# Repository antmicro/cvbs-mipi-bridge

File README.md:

# Composite Video (CVBS) to MIPI CSI-2 bridge

Copyright (c) 2022-2025 [Antmicro](https://www.antmicro.com)

## Overview

This repository contains open hardware design files for a video bridge converting the analog composite video (CBVS) standard into MIPI CSI-2.
The video conversion is handled with Analog Devices [ADV7828-M](https://www.analog.com/media/en/technical-documentation/data-sheets/ADV7282.pdf) 10-bit 4x Oversampled SDTV Video Decoder.
The design files were prepared in KiCad.

## Repository structure

The main repository directory contains KiCad PCB project files, a LICENSE and README.
The remaining files are stored in the following directories:

* `lib` - contains the component libraries
* `img` - contains graphics for this README
* `doc` - contains pdf schematics
* `assets` - contains visual assets for showcasing this design on [Open Hardware Portal](https://openhardware.antmicro.com)

## Key Features

* Analog Devices ADV7282-M CVBS-to-MIPI video converter
* 4 analog video input channels exposed on RCA connectors
* A single 1-lane MIPI CSI-2 digital output interface

Please note that according to the datasheet the ADV7282-M includes an embedded analog multiplexer and processes only one analog input channel at a time.

This video accessory is electrically compatible with several video processing platforms created by Antmicro, such as:
 
* [Jetson Nano Baseboard](https://github.com/antmicro/jetson-nano-baseboard) supporting NVIDIA Jetson Nano, Jetson Xavier NX, Jetson TX2 NX
* [Google Coral Baseboard](https://github.com/antmicro/google-coral-baseboard)
* [Snapdragon 625 Baseboard](https://github.com/antmicro/snapdragon-625-baseboard)
* [Snapdragon 845 Baseboard](https://github.com/antmicro/snapdragon-845-baseboard)
* [AMD-Xilinx Kria K26 DevBoard](https://github.com/antmicro/kria-k26-devboard)

It can also be used with NVIDIA AGX Xavier and NVIDIA AGX Orin with a dedicated [adapter](https://github.com/antmicro/jetson-agx-csi-adapter).

## Board diagram

## License

[Apache-2.0](LICENSE)

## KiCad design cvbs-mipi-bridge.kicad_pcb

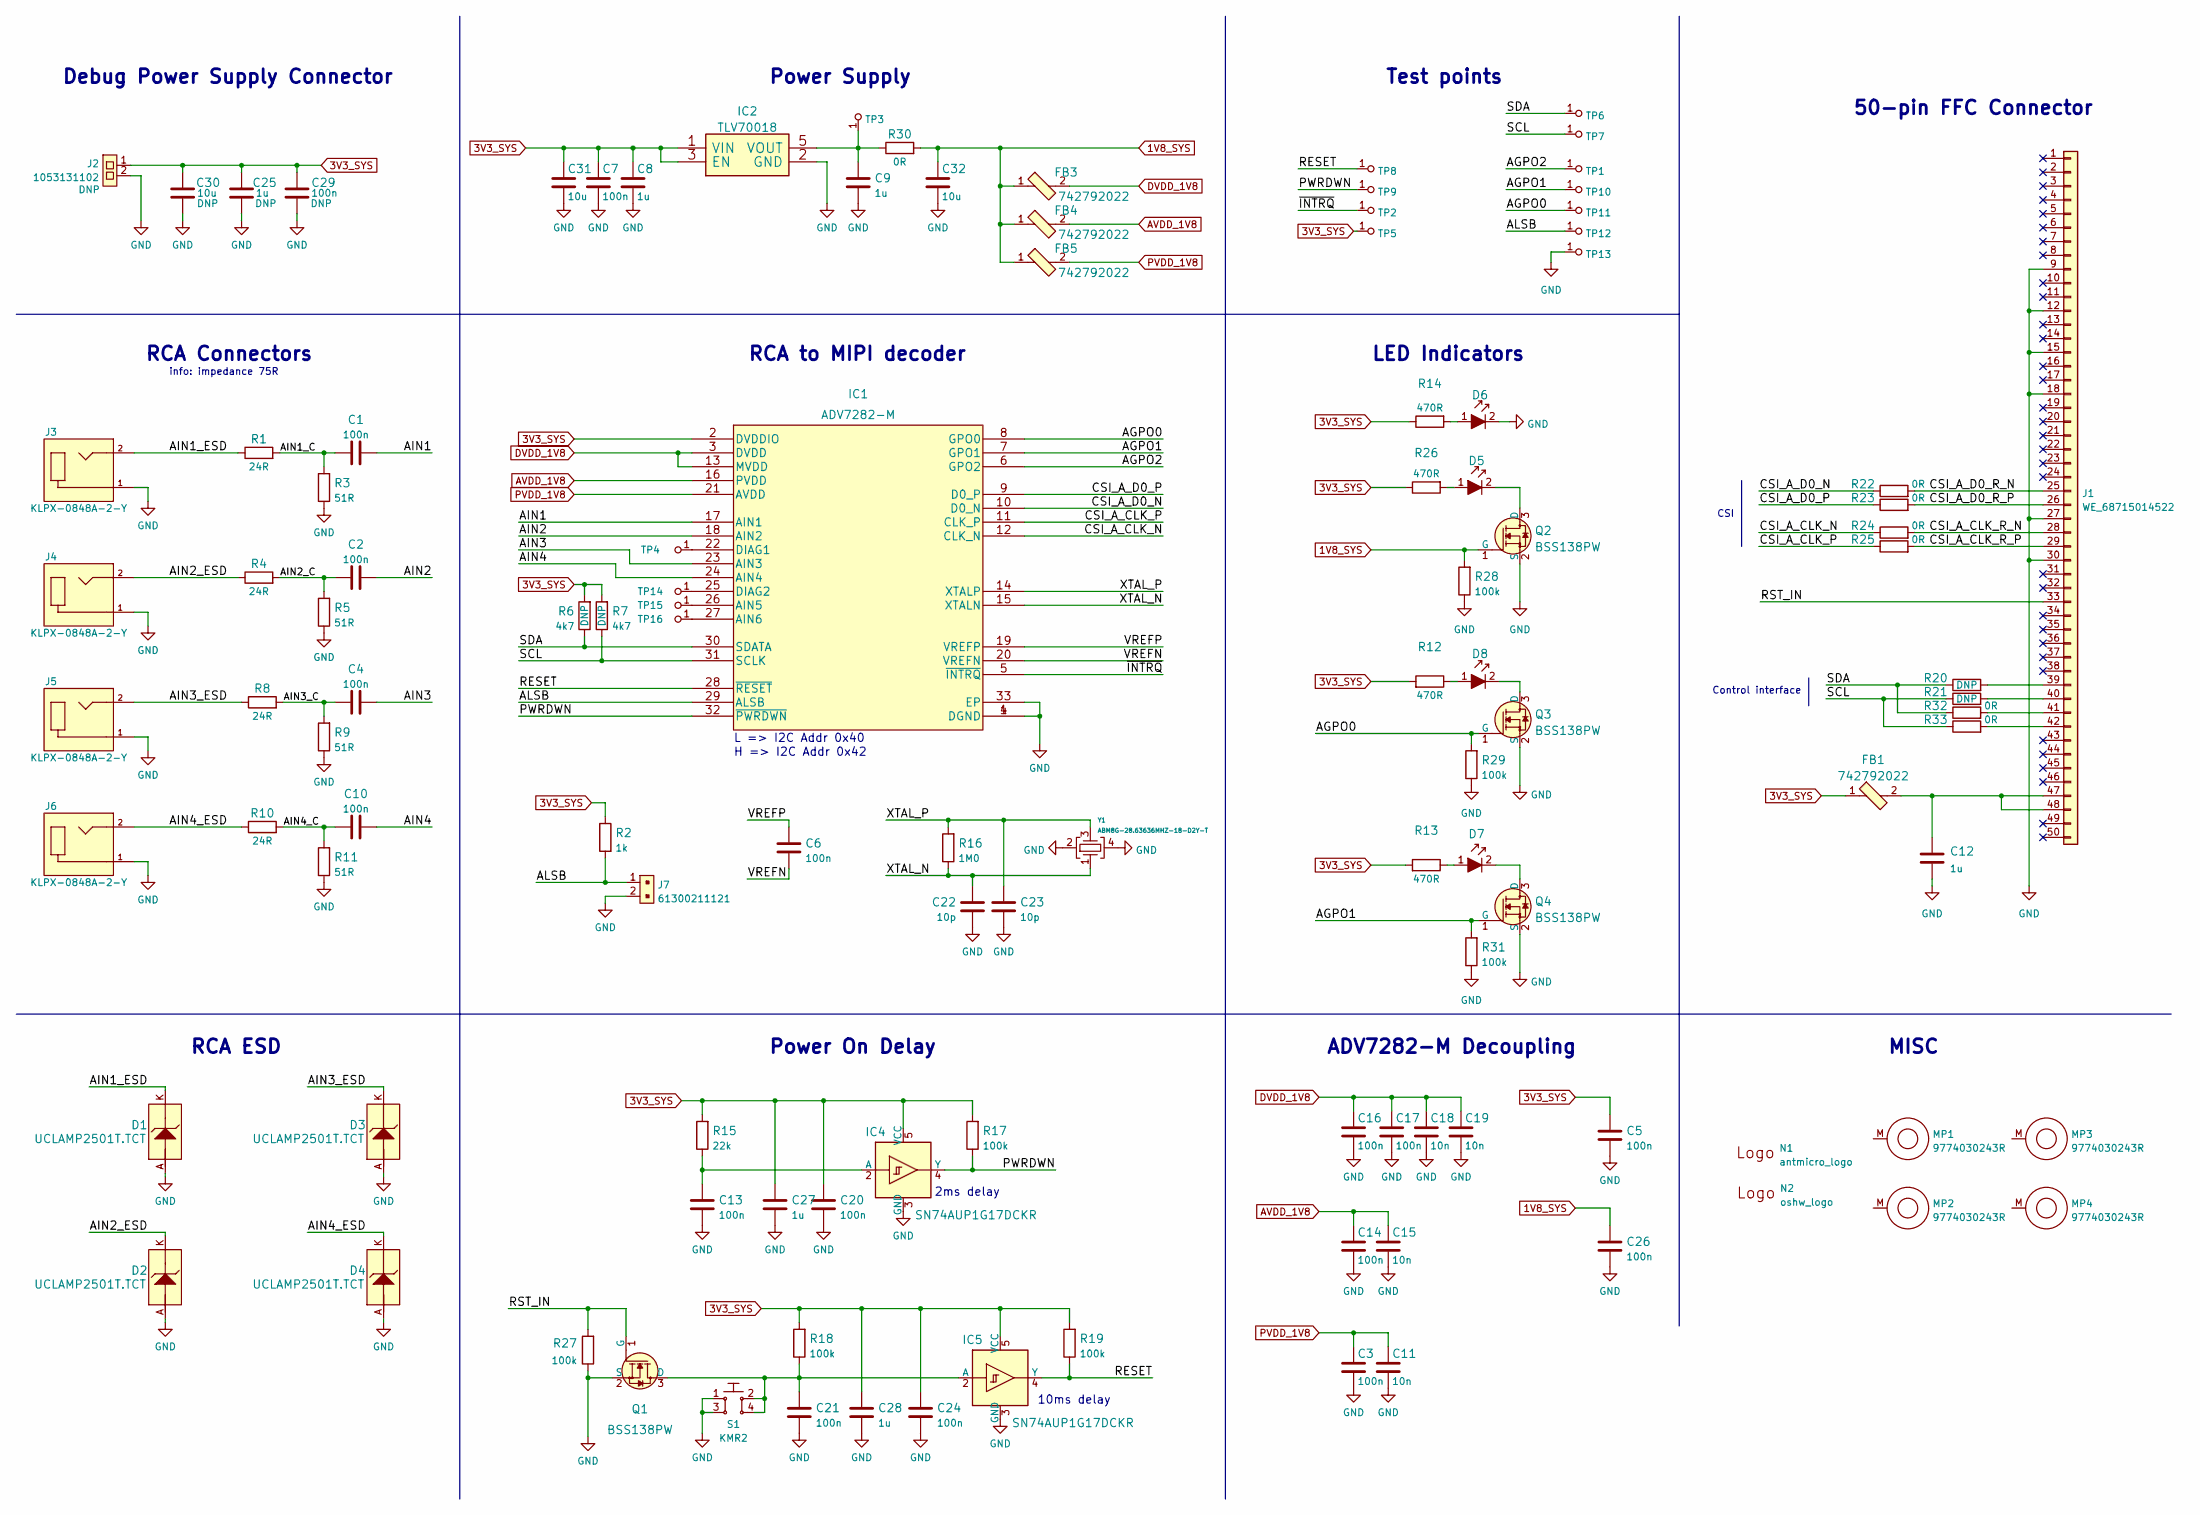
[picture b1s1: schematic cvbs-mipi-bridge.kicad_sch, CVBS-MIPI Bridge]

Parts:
C1, C2, C3, C4, C5, C6, C7, C10, C14, C16, C17, C26, C29: C_100n_0402; 0402-cap; MPN GRM155R61H104KE14D
C8, C9, C25: C_1u_0402; 0402-cap; MPN C1005X6S1A105K050BC
C11, C15, C18, C19: C_10n_0402; 0402-cap; MPN 04025G103ZAT2A
C12: C_1u_0603; 0603-cap; MPN 0603YD105KAT2A
C13, C20, C21, C24: C_100n_0402; 0402-cap_ThermalReliefs_ZoneSizeSettings; MPN GRM155R61H104KE14D
C22, C23: C_10p_0402; 0402-cap; MPN MC0402N100D500CT
C27, C28: C_1u_0402; 0402-cap_ThermalReliefs_ZoneSizeSettings; MPN C1005X6S1A105K050BC
C30, C31, C32: C_10u_0603; 0603-cap; MPN GRM188R61A106KE69D
D1, D2, D3, D4: UCLAMP2501T.TCT; SLP1006P2T; MPN UCLAMP2501T.TCT
D5, D7, D8: KP-1608ZGC; LED_0603; MPN KP-1608EC
D6: KP-1608ZGC; LED_0603_ThermalReliefs_ZoneSizeSettings; MPN KP-1608EC
FB1, FB3, FB4, FB5: 742792022; 0805-res; MPN 742792022
IC1: ADV7282-M; LFCSP-32-1EP-5x5mm; MPN ADV7282WBCPZ-M
IC2: TLV70018; SC-70-5; MPN TLV70018DCKR
IC4, IC5: SN74AUP1G17DCKR; SC-70-5; MPN SN74AUP1G17DCKR
J1: WE_68715014522; MPN 68715014522
J2: 1053131102; MPN 1053131102
J3, J4, J5, J6: KLPX-0848A-2-Y; MPN KLPX-0848A-2-Y
J7: 61300211121; PinHeader_1x2_P2.54_Drill0.9mm; MPN 61300211121
MP1, MP2, MP3, MP4: 9774030243R; MPN 9774030243R
N1: antmicro_logo; antmicro-logo_scaled_20mm_mask
N2: oshw_logo; oshw-logo
Q1, Q2, Q3, Q4: BSS138PW; SC70-3; MPN BSS138PW
R1, R4, R8, R10: R_24R_0402; 0402-res; MPN ERJ-2RKF24R0X
R2: R_1k_0402; 0402-res; MPN CR0402-FX-1001GLF
R3, R5, R9, R11: R_51R_0402; 0402-res; MPN RC0402FR-0751RL
R6, R7: R_4k7_0402; 0402-res; MPN MCS04020C4701FE000
R12, R13, R14, R26: R_470R_0402; 0402-res; MPN CRCW0402470RFKED
R15: R_22k_0402; 0402-res; MPN ERJ-2RKF2202X
R16: R_1M0_0402; 0402-res; MPN CRG0402F1M0
R17, R18, R19: R_100k_0402; 0402-res; MPN CRCW0402100KFKEDHP
R20, R21, R22, R23, R24, R25, R32, R33: R_0R_0402; 0402-res; MPN ERJ2GE0R00X
R27, R28, R29, R31: R_100k_0402; 0402-res_ThermalReliefs_ZoneSizeSettings; MPN CRCW0402100KFKEDHP
R30: R_0R_0805; 0805-res; MPN CRCW08050000Z0EA
S1: KMR2; SW_SPST_4.2x2.8_ThermalReliefs_ZoneSizeSettings; MPN KMR211NGLFS
TP1, TP2, TP3, TP4, TP5, TP6, TP7, TP8, TP9, TP10, TP11, TP12, TP13, TP14, TP15, TP16: TP; TP-R-1.5
Y1: ABM8G-28.63636MHZ-18-D2Y-T; KX-7; MPN ABM8G-25.000MHZ-18-D2Y-T

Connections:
1V8_SYS: C26.2, C32.1, FB3.1, FB4.1, FB5.1, Q2.1 (G), R28.2, R30.2
3V3_SYS: C5.2, C7.2, C8.1, C20.1, C24.1, C25.1, C27.1, C28.1, C29.2, C30.1, C31.1, FB1.1, IC1.2 (DVDDIO), IC2.1 (VIN), IC2.3 (EN), IC4.5 (VCC), IC5.5 (VCC), J2.1, R2.1, R6.2, R7.2, R12.2, R13.2, R14.1, R15.2, R17.2, R18.2, R19.2, R26.1, TP5.1
/AGPO0: IC1.8 (GPO0), Q3.1 (G), R29.2, TP11.1
/AGPO1: IC1.7 (GPO1), Q4.1 (G), R31.2, TP10.1
/AGPO2: IC1.6 (GPO2), TP1.1
/AIN1: C1.2, IC1.17 (AIN1)
/AIN1_C: C1.1, R1.2, R3.2
/AIN1_ESD: D1.K, J3.2, R1.1
/AIN2: C2.2, IC1.18 (AIN2)
/AIN2_C: C2.1, R4.2, R5.2
/AIN2_ESD: D2.K, J4.2, R4.1
/AIN3: C4.2, IC1.23 (AIN3)
/AIN3_C: C4.1, R8.2, R9.2
/AIN3_ESD: D3.K, J5.2, R8.1
/AIN4: C10.2, IC1.24 (AIN4)
/AIN4_C: C10.1, R10.2, R11.2
/AIN4_ESD: D4.K, J6.2, R10.1
/ALSB: IC1.29 (ALSB), J7.1, R2.2, TP12.1
/CSI_A_CLK_N: IC1.12 (CLK_N), R24.1
/CSI_A_CLK_P: IC1.11 (CLK_P), R25.1
/CSI_A_CLK_R_N: J1.28, R24.2
/CSI_A_CLK_R_P: J1.29, R25.2
/CSI_A_D0_N: IC1.10 (D0_N), R22.1
/CSI_A_D0_P: IC1.9 (D0_P), R23.1
/CSI_A_D0_R_N: J1.25, R22.2
/CSI_A_D0_R_P: J1.26, R23.2
/PWRDWN: IC1.32 (~PWRDWN), IC4.4 (Y), R17.1, TP9.1
/RESET: IC1.28 (~RESET), IC5.4 (Y), R19.1, TP8.1
/RST_IN: J1.33, Q1.1 (G), R27.2
/SCL: IC1.31 (SCLK), R7.1, R21.1, R33.1, TP7.1
/SDA: IC1.30 (SDATA), R6.1, R20.1, R32.1, TP6.1
/VREFN: C6.1, IC1.20 (VREFN)
/VREFP: C6.2, IC1.19 (VREFP)
/XTAL_N: C22.1, IC1.15 (XTALN), R16.1, Y1.1
/XTAL_P: C23.1, IC1.14 (XTALP), R16.2, Y1.3
/~INTRQ: IC1.5 (~INTRQ), TP2.1
AVDD_1V8: C14.2, C15.1, FB4.2, IC1.16 (PVDD)
DVDD_1V8: C16.2, C17.2, C18.1, C19.1, FB3.2, IC1.3 (DVDD), IC1.13 (MVDD)
GND: C3.1, C5.1, C7.1, C8.2, C9.2, C11.2, C12.2, C13.2, C14.1, C15.2, C16.1, C17.1, C18.2, C19.2, C20.2, C21.2, C22.2, C23.2, C24.2, C25.2, C26.1, C27.2, C28.2, C29.1, C30.2, C31.2, C32.2, D1.A, D2.A, D3.A, D4.A, D6.2, IC1.1 (DGND), IC1.4 (DGND), IC1.33 (EP), IC2.2 (GND), IC4.3 (GND), IC5.3 (GND), J1.9, J1.12, J1.15, J1.18, J1.27, J1.30, J2.2, J3.1, J4.1, J5.1, J6.1, J7.2, Q1.2 (S), Q2.2 (S), Q3.2 (S), Q4.2 (S), R3.1, R5.1, R9.1, R11.1, R27.1, R28.1, R29.1, R31.1, S1.1, S1.3, TP13.1, Y1.2, Y1.4
unnamed: C9.1, IC2.5 (VOUT), R30.1, TP3.1
unnamed: C12.1, FB1.2, J1.47, J1.48
unnamed: C13.1, IC4.2 (A), R15.1
unnamed: C21.1, IC5.2 (A), Q1.3 (D), R18.1, S1.2, S1.4
unnamed: D5.1, R26.2
unnamed: D5.2, Q2.3 (D)
unnamed: D6.1, R14.2
unnamed: D7.1, R13.1
unnamed: D7.2, Q4.3 (D)
unnamed: D8.1, R12.1
unnamed: D8.2, Q3.3 (D)
unnamed: IC1.22 (DIAG1), TP4.1
unnamed: IC1.25 (DIAG2), TP14.1
unnamed: IC1.26 (AIN5), TP15.1
unnamed: IC1.27 (AIN6), TP16.1
unnamed: J1.39, R20.2
unnamed: J1.40, R21.2
unnamed: J1.41, R32.2
unnamed: J1.42, R33.2
PVDD_1V8: C3.2, C11.1, FB5.2, IC1.21 (AVDD)

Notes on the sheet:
10ms delay
50-pin FFC Connector
MISC
Debug Power Supply Connector
LED Indicators
Power Supply
Power On Delay
L => I2C Addr 0x40
ADV7282-M Decoupling
CSI
RCA to MIPI decoder
info: impedance 75R
Test points
RCA Connectors
H => I2C Addr 0x42
2ms delay
Control interface
RCA ESD

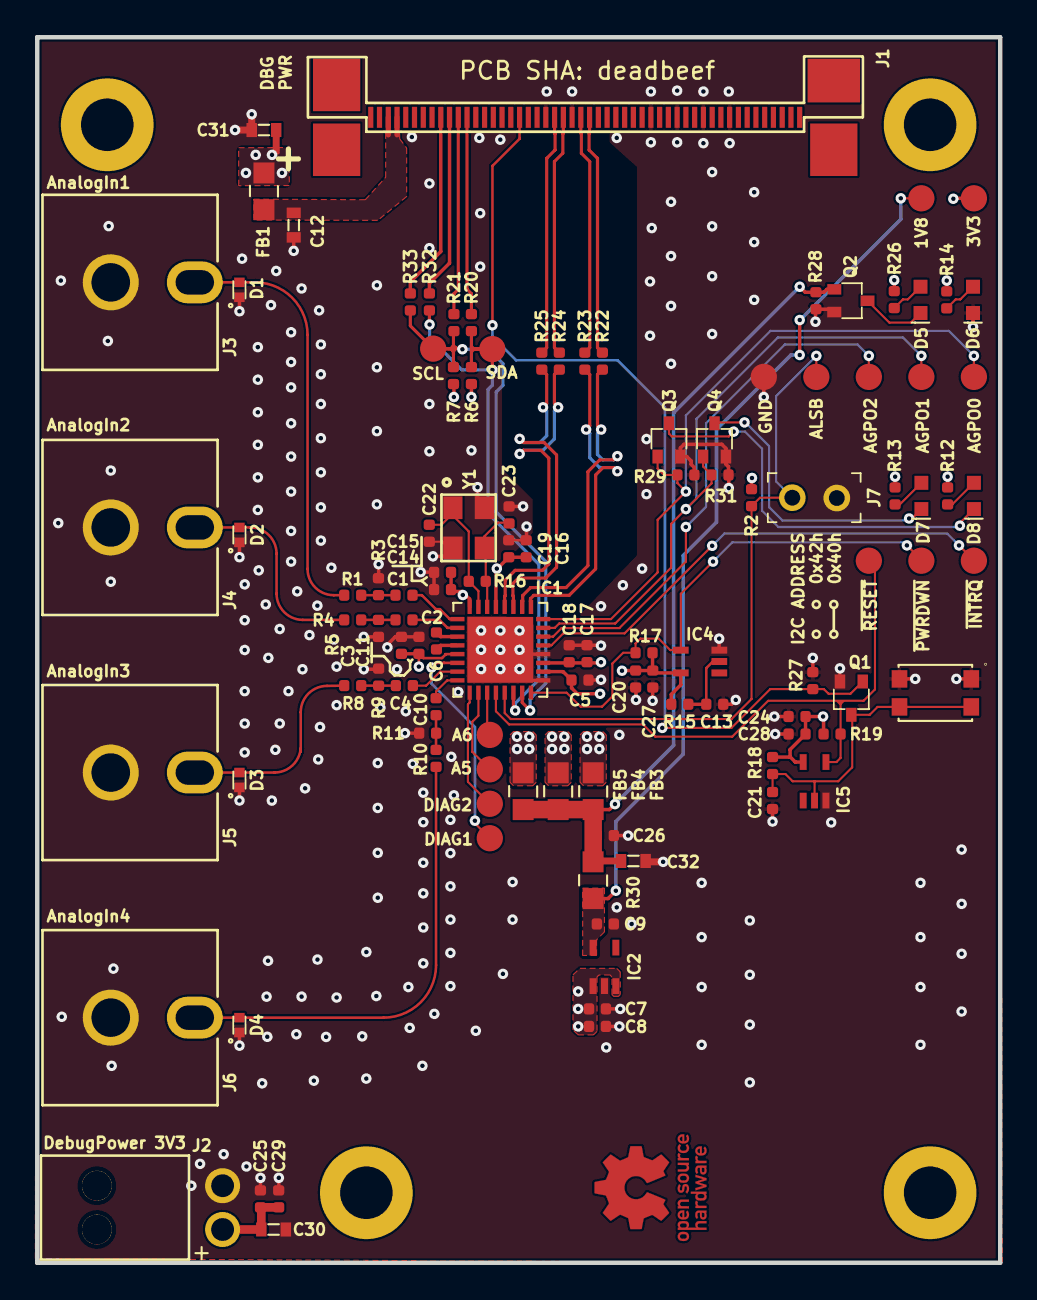
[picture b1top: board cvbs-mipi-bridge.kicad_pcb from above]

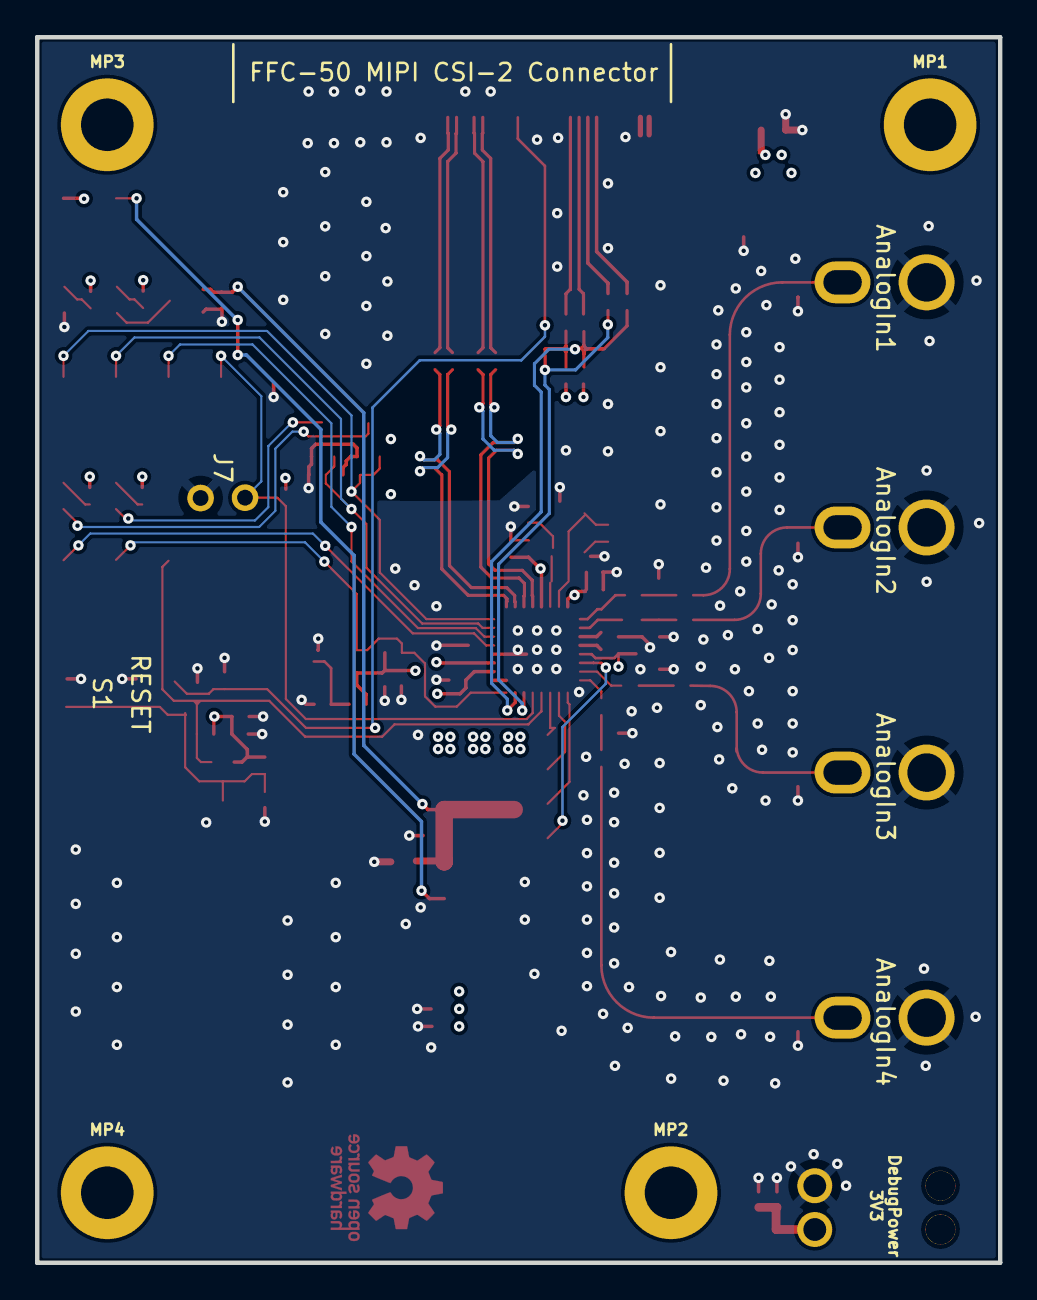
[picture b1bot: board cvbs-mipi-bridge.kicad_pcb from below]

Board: 4 copper layers, 55.0 x 70.0 mm, 116 parts (4 on the bottom side), 59 nets.

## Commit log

2022-09-06 Initial commit, add Altium Design Files
2022-09-07 Initial convertion commit. Changed Outputs to Altium-Outputs
2022-09-07 Moved Altium project legacy files into separate folder
2022-09-07 Started converting schematics to antmicro-kicad-library
2022-09-08 Finished correcting schematics
2022-09-08 Reordered components on schematic. Bumped revision to 1.2.0
2022-09-08 Defined net classes
2022-09-08 Started component positions adjusment and placement
2022-09-09 Finished placement. Removed 5V net and components. Started routing
2022-09-12 Finished and optimized routing on PCB
2022-09-12 Schematic review fixes
2022-09-12 Fixes adjusted visually. New components annotated
2022-09-14 Corrected PCB after review
2022-09-14 loclib. Added new components from schematic after review
2022-09-14 Corrected ADV7280 footprint. Finished corrections and optimizations. Added missing step model
2022-09-29 Cleanup
2022-09-29 Replace RCA connectors
2022-09-29 Add README
2022-09-29 Add LICENSE
2022-09-29 Replace TVS diodes
2022-09-29 Chip replaced with ADV7282-M
2022-09-29 Replace DC power connector
2022-09-29 Routing (WiP)
2022-09-29 Update designators
2022-09-29 Update naming convention, assign revision 1.0.0, update signage on PCB
2022-09-29 Rearrange components (WiP)
2022-09-29 Rearrange connectors (WiP)
2022-09-29 Place components, route video signals
2022-09-29 Loclib
2022-09-29 Testpoints added
2022-09-29 Routed auxiliary signals
2022-09-29 Connected GNDs, cleaned DRC
2022-09-29 Updated zones
2022-09-29 Via stiching
2022-09-30 Add coupling capacitors
2022-09-30 EC E1451374
2022-10-12 Mark C30 as DNP, improve it's clarity on schematic
2022-10-19 Notes added by 'git notes add'
2022-12-07 PCB: Clean up doubled IC1 reference designator on F.Silkscreen
2022-12-07 Update SN74AUP1G17DCKR in local library, fix local library structure
2022-12-07 Update SN74AUP1G17DCKR symbol in local library
    Most notable: Changed footprint to SC-70-5 which is already used by IC2 in this project & has 3D STEP & Blender model
2022-12-07 Update SN74AUP1G17DCKR symbol on SCH from local library
2022-12-07 Update local SC70-3 footprint from global library
2022-12-07 Remove unused SOT footprints and their STEP 3D models from local library
2022-12-07 Remove old, unused RCA Connector footprint & it's 3D model from local lib
2022-12-07 Update Q1-Q4 from global library on SCH and PCB
2022-12-07 Reroute tracks after updating IC4, IC5, Q1-4 footprint
2022-12-07 PCB: Fix DRC errors & warnings
    - Move GND Via near C10 & C4, which collided with PVDD_1V8 power line on In2.Cu layer
    - Move Q1-Q4, IC2-5 Reference Designators around on F. Silkscreen
2022-12-07 PCB: Move Reference Designators clipped by un-tented vias
2022-12-07 Increase revision number to 1.0.1 - update title blocks & PCB marking
2022-12-07 Correct F.Cu's main GND Copper Zone's minimal clearance and width to Eurocircuits Pattern Class 7
2022-12-07 Update selected footprints to KiCad 6 format
2022-12-07 Add thermal relief versions of 0402 passives' footprints, fix metadata
    - Fixed Description, Value and Keywords for 0402-cap (it was described as a Resistor)
2022-12-07 Make thermal-relief versions of two-lead footprints in project lib
    These are with Thermal Relief Spoke Width & Gap Clearance inherited from Copper Zone settings
2022-12-07 Update 0603 footprints from library
2022-12-07 Change F.Cu's GND plane thermal relief sizes to 0.125mm clearance, 0.2mm spoke width
2022-12-07 SCH: Change selected Power On Delay elements' footprints to thermal-relief variants
    Thermal reliefs added to: R27, C13, C20, C21, C24, C27, C28
2022-12-07 SCH: Change selected LED Indicators' section elements to thermal-relief variatns
    These are: D6, R28, R29, R31
2022-12-07 Update PCB from SCH after changing selected symbols' footprints
2022-12-07 Refill copper zones after PCB update
2022-12-07 Increase Default net-class track width to 0.2 mm
2022-12-07 Make 3V3_SYS power tracks between IC1,IC4,IC5 use Net-class width (0.2mm)
    - 3V3_SYS Track width increased from 0.125 mm to 0.2mm, zones re-filled
    - Re-routed some tracks for improved aesthetics and optimised thermal reliefs
2022-12-07 Change S1 footprint to thermal-relief version
2022-12-07 Tidy up DVDD_1V8 track near IC1 pin 3
    - Re-route with a single straight track
    - Increase track width to 0.2mm, like on other power-rails
2022-12-07 Fix/improve F.Silkscreen, adjust 2 GND vias to fit
2022-12-07 Uniformize F.Silkscreen text to 0.65mm size, 0.15mm thickness; adjust position where needed
2022-12-07 Refill copper zones
2022-12-07 Board Setup: Change soldermask, silkscreen and copper plating to prototype's colors.
2022-12-07 Improve F. Silkscreen, fine-tune board/soldermask color for KiCad 3D Viewer
2022-12-07 Fix DRC errors: LED RefDes's moved, 3V3_SYS track near C20 rerouted
2022-12-07 Clean-up F.Fab layer
2022-12-07 Add connectors & button descriptions to B.Silkscreen
2022-12-07 SCH: Cosmetic improvements
    - Add labels for AGPO2 and ~INTRQ
    - Move their Test Points to "Test points" section
    - Rearrange "Test points" section to somewhat resemble actual test point placement on PCB
    - Uniformize local label font size to 1.524 mm, except for AIN nets in RCA Connectors section
2022-12-07 Update PCB nets from SCH
2022-12-07 Update antmicro_logo footprint reference to correct one
    Update in local library, then on SCH, then updated PCB from SCH
2022-12-07 Increase design revision number to 1.0.2 - update title blocks and date
2022-12-07 Remove unused F.Cu variant of antmicro_logo
2022-12-07 Add second pair of resistors for re-connecting I2C.
2022-12-07 Bump PCB revision to 1.2.0
2022-12-07 Generate PDF schematic
2022-12-07 README: Add photo
2022-12-07 Update photo
2022-12-07 Add OSP link
2023-10-13 Introduce project standardization
2023-10-13 [#50306] Add OHP assets and schematic PDF
2024-03-20 [#56797] Fix lib references
2024-03-22 Upload assets
2024-03-26 [#56797] Loclib
2024-03-26 [#56797] Update revision & date
2024-03-28 [#56797] Mark components DNP
2024-03-28 [#56797] Recalculate copper pours
2025-03-21 [#74509] Add SI assets
